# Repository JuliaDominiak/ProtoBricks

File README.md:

# ProtoBricks
## code_brickPlate_4x4<br />
The version is designed for a 4x4 tile<br />

 * **Brickplate_mini.ino** - the main program<br />
 * **MPR_connections.ino** - connecting with touch and color sensors<br />
 * **cap_1.ino** - displaying data from the first sensor<br />
 * **cap_2.ino** - displaying data from the second sensor<br />
 * **color.ino** - perform a color scan and decode RGB values<br />
 * **location.ino** - locate the pin for spike detection<br />
 * **decoding.ino** - decoding the location.ino number from the pin to the XY coordinates<br />

| Color  |No.|               
| ------ | - |               
| Red    | 1 |
| Blue   | 2 |
| Grey   | 3 |               
| Orange | 4 |               
| Yellow | 5 |
| Green  | 6 |

Touch sensor addresses - 0x5C, 0x5A<br />
Touch detection threshold: 150<br />

Pin functions<br />
pin 10 - adding / removing bricks<br />
pin 8 - color detection<br />

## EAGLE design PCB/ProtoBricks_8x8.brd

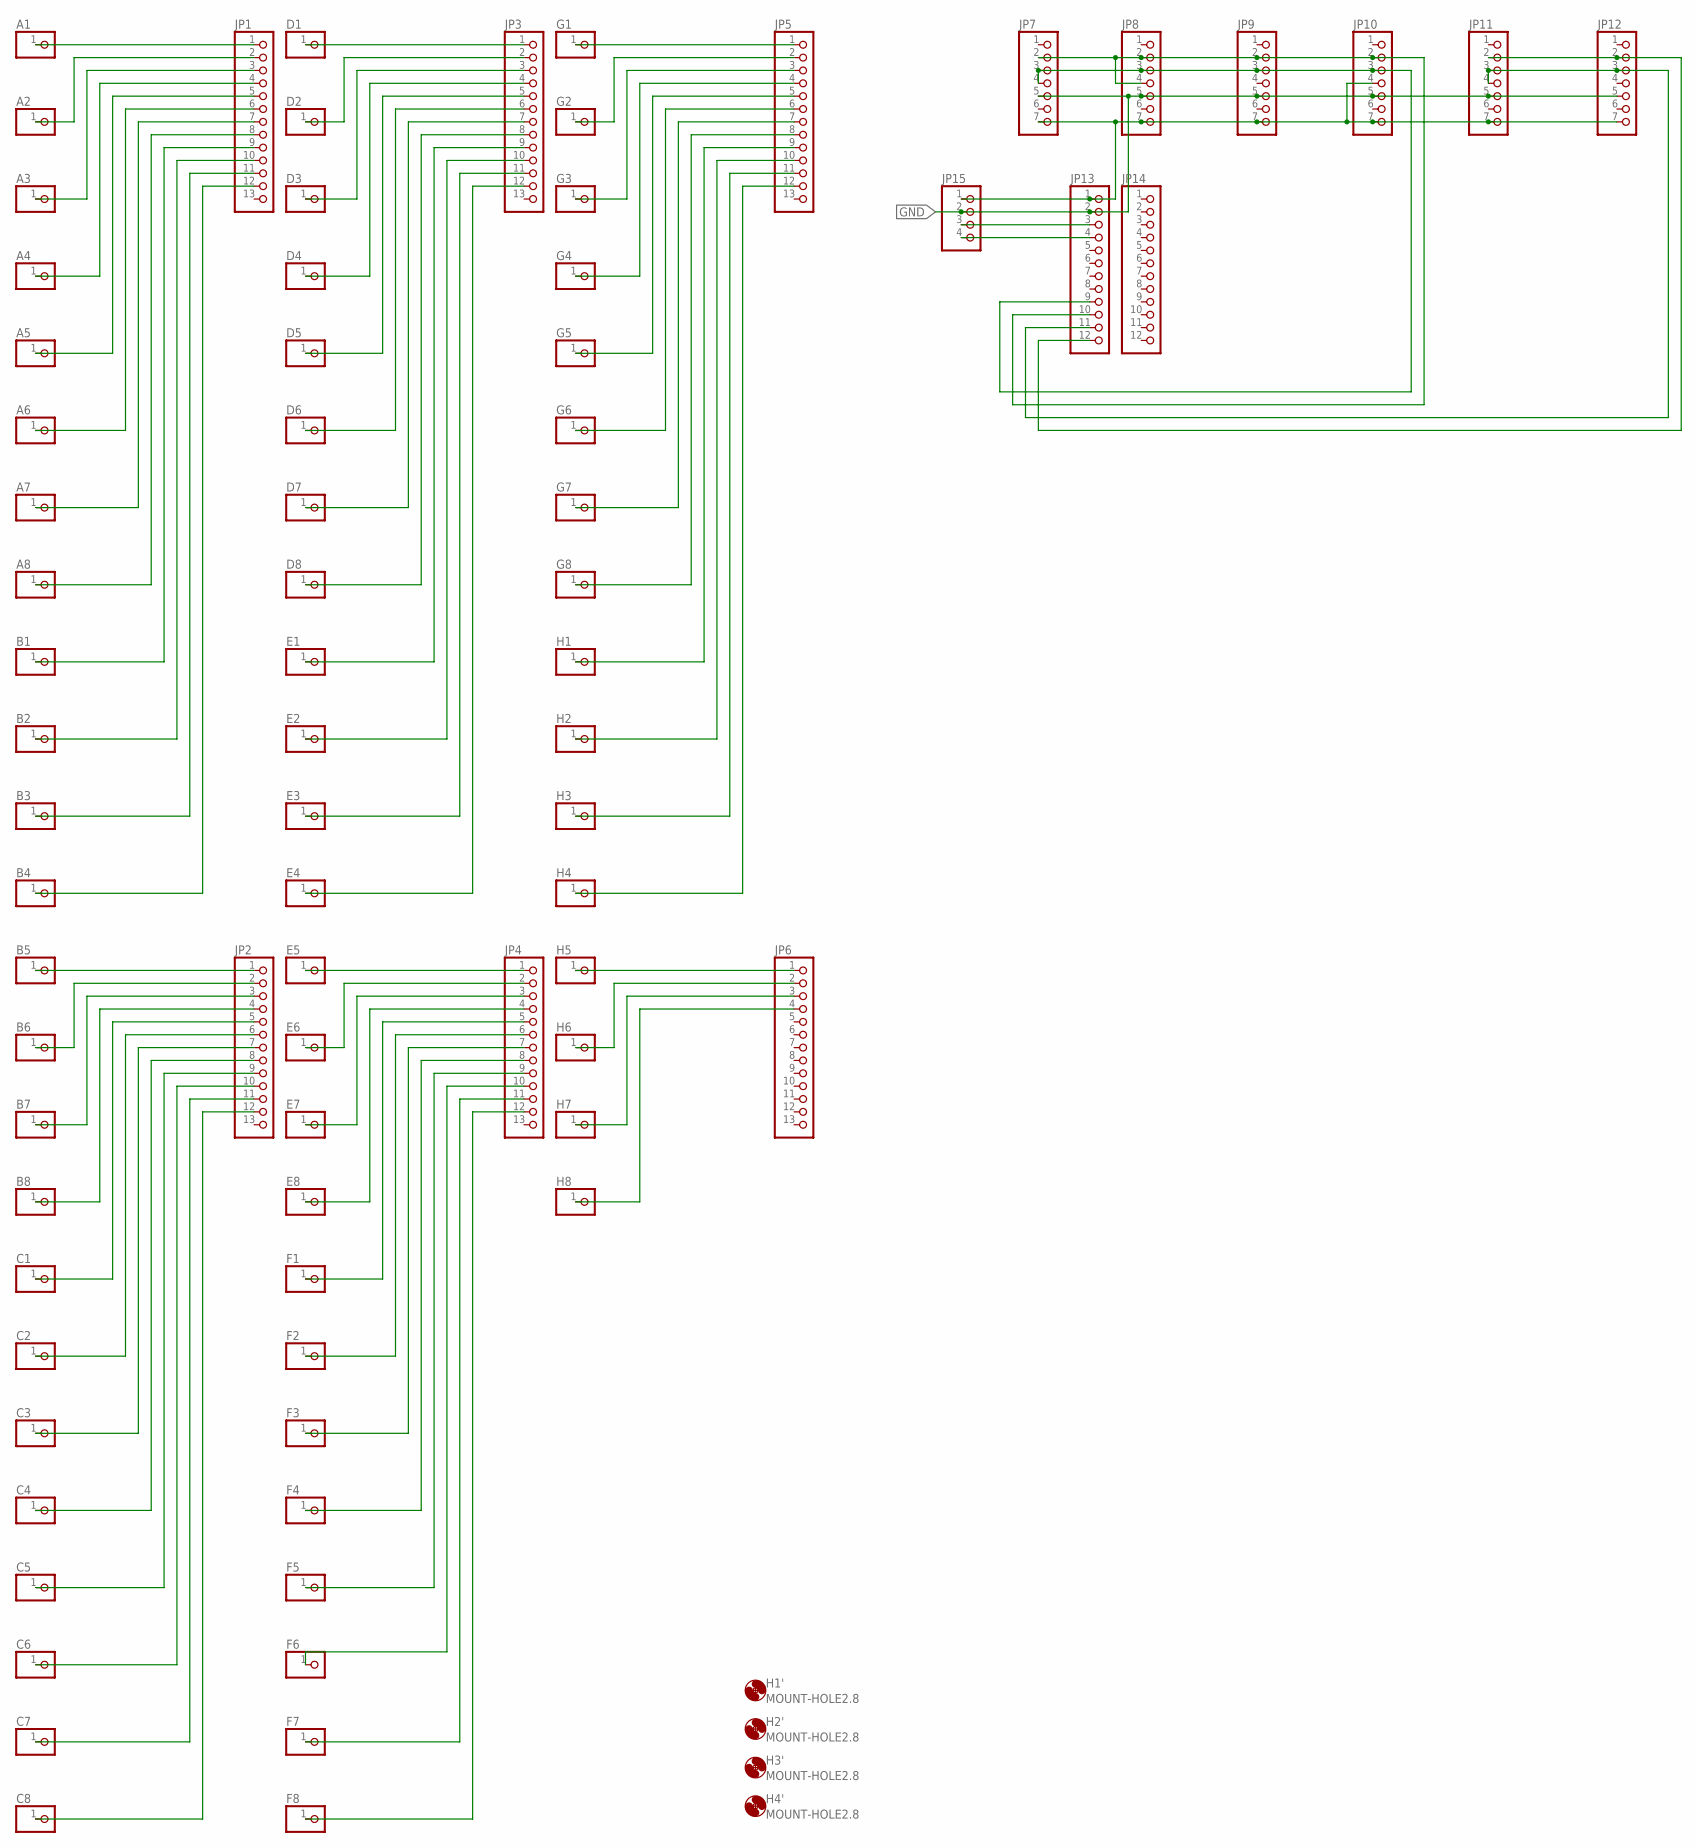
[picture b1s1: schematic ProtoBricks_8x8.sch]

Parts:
A1, A2, A3, A4, A5, A6, A7, A8: PINHD-1X1; 1X01
B1, B2, B3, B4, B5, B6, B7, B8: PINHD-1X1; 1X01
C1, C2, C3, C4, C5, C6, C7, C8: PINHD-1X1; 1X01
D1, D2, D3, D4, D5, D6, D7, D8: PINHD-1X1; 1X01
E1, E2, E3, E4, E5, E6, E7, E8: PINHD-1X1; 1X01
F1, F2, F3, F4, F5, F6, F7, F8: PINHD-1X1; 1X01
G1, G2, G3, G4, G5, G6, G7, G8: PINHD-1X1; 1X01
H1, H2, H3, H4, H5, H6, H7, H8: PINHD-1X1; 1X01
H1', H2', H3', H4': MOUNT-HOLE2.8; 2,8
JP1, JP2, JP3, JP4, JP5, JP6: PINHD-1X13; 1X13
JP7, JP8, JP9, JP10, JP11, JP12: PINHD-1X7; 1X07
JP13, JP14: PINHD-1X12; 1X12
JP15: PINHD-1X4; 1X04

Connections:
GND: JP7.5, JP8.5, JP9.5, JP10.5, JP11.5, JP12.5, JP13.2, JP15.2
unnamed: A1.1, JP1.1
unnamed: A2.1, JP1.2
unnamed: B5.1, JP2.1
unnamed: A3.1, JP1.3
unnamed: A4.1, JP1.4
unnamed: A5.1, JP1.5
unnamed: A6.1, JP1.6
unnamed: A7.1, JP1.7
unnamed: A8.1, JP1.8
unnamed: B1.1, JP1.9
unnamed: C8.1, JP2.12
unnamed: C7.1, JP2.11
unnamed: C6.1, JP2.10
unnamed: C5.1, JP2.9
unnamed: C4.1, JP2.8
unnamed: B2.1, JP1.10
unnamed: C3.1, JP2.7
unnamed: C2.1, JP2.6
unnamed: C1.1, JP2.5
unnamed: B8.1, JP2.4
unnamed: D1.1, JP3.1
unnamed: B7.1, JP2.3
unnamed: B6.1, JP2.2
unnamed: D2.1, JP3.2
unnamed: B3.1, JP1.11
unnamed: D3.1, JP3.3
unnamed: D4.1, JP3.4
unnamed: D5.1, JP3.5
unnamed: D6.1, JP3.6
unnamed: D7.1, JP3.7
unnamed: D8.1, JP3.8
unnamed: B4.1, JP1.12
unnamed: E1.1, JP3.9
unnamed: E2.1, JP3.10
unnamed: E3.1, JP3.11
unnamed: E4.1, JP3.12
unnamed: E5.1, JP4.1
unnamed: E6.1, JP4.2
unnamed: E7.1, JP4.3
unnamed: E8.1, JP4.4
unnamed: G1.1, JP5.1
unnamed: G2.1, JP5.2
unnamed: G3.1, JP5.3
unnamed: G4.1, JP5.4
unnamed: G5.1, JP5.5
unnamed: G6.1, JP5.6
unnamed: G7.1, JP5.7
unnamed: G8.1, JP5.8
unnamed: H1.1, JP5.9
unnamed: H2.1, JP5.10
unnamed: H3.1, JP5.11
unnamed: H4.1, JP5.12
unnamed: H5.1, JP6.1
unnamed: H6.1, JP6.2
unnamed: H7.1, JP6.3
unnamed: H8.1, JP6.4
unnamed: F1.1, JP4.5
unnamed: F2.1, JP4.6
unnamed: F3.1, JP4.7
unnamed: F4.1, JP4.8
unnamed: F5.1, JP4.9
unnamed: F6.1, JP4.10
unnamed: F7.1, JP4.11
unnamed: F8.1, JP4.12
unnamed: JP7.2, JP8.2, JP8.4, JP9.2, JP10.2, JP13.10
unnamed: JP7.3, JP7.4, JP8.3, JP9.3, JP10.3, JP13.9
unnamed: JP11.2, JP12.2, JP13.12
unnamed: JP11.3, JP11.4, JP12.3, JP13.11
unnamed: JP7.7, JP8.7, JP9.7, JP10.4, JP10.7, JP11.7, JP12.7, JP13.1, JP15.1
unnamed: JP13.3, JP15.3
unnamed: JP13.4, JP15.4

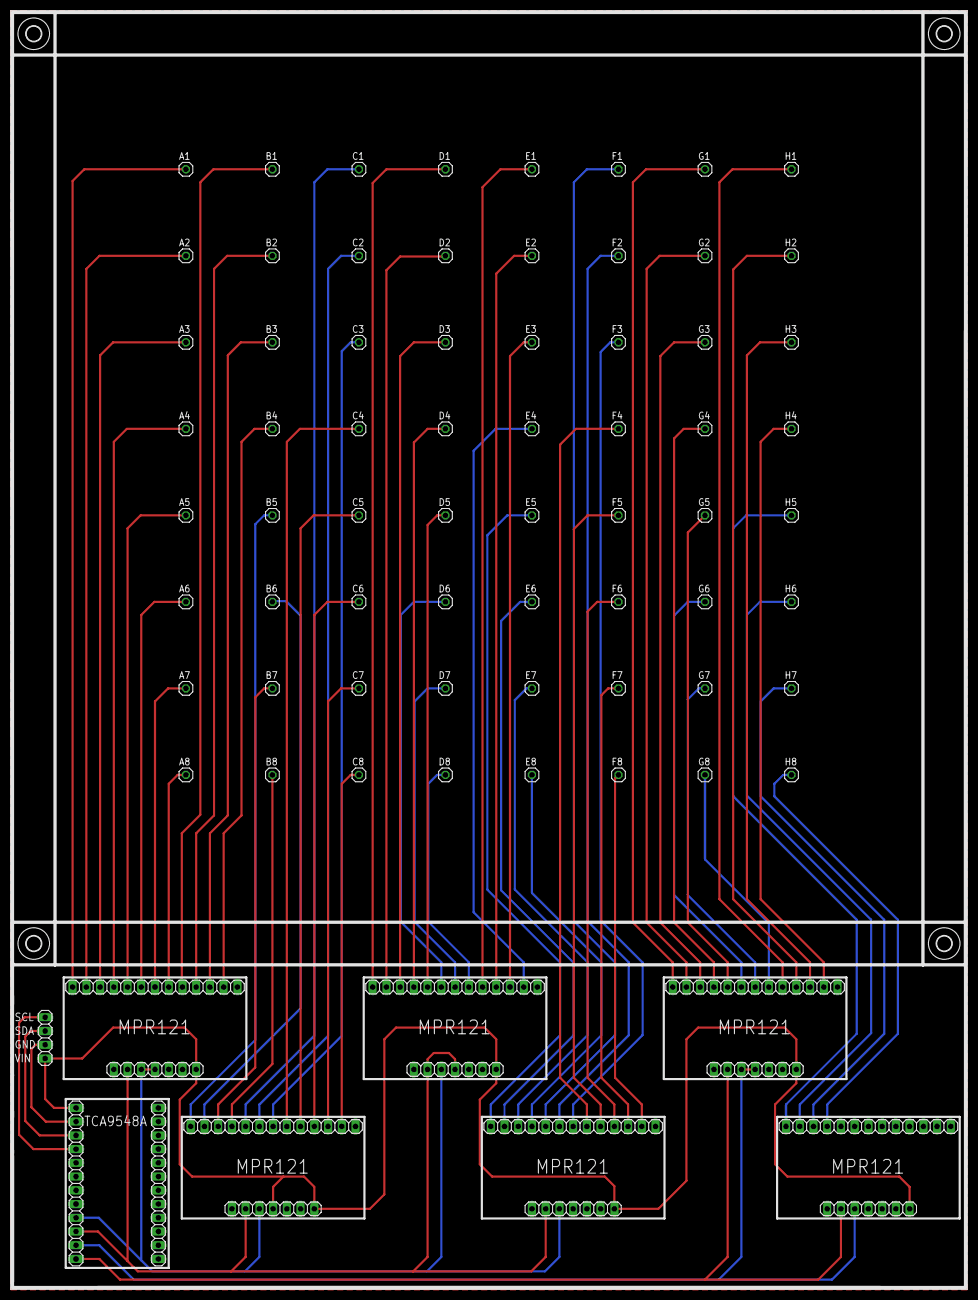
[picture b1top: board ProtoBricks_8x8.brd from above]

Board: 2 copper layers, 176.9 x 236.4 mm, 83 parts (0 on the bottom side), 72 nets.

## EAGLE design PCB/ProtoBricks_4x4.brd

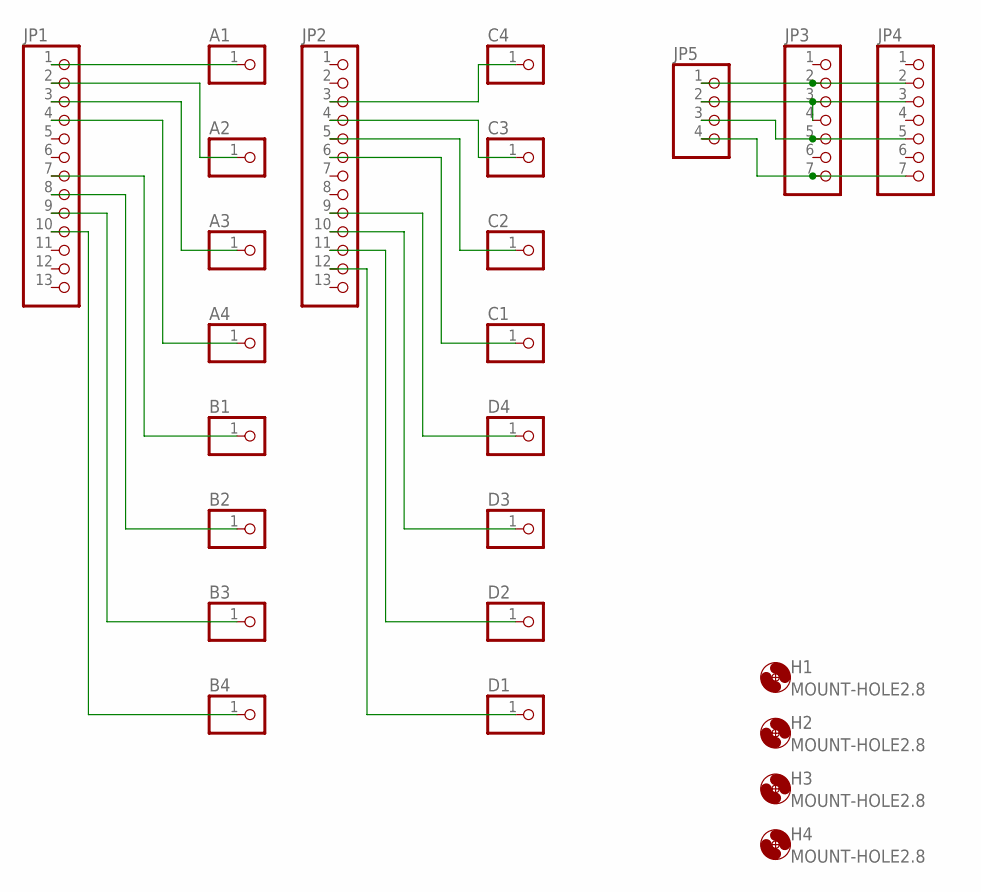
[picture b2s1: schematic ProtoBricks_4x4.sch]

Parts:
A1, A2, A3, A4: PINHD-1X1; 1X01
B1, B2, B3, B4: PINHD-1X1; 1X01
C1, C2, C3, C4: PINHD-1X1; 1X01
D1, D2, D3, D4: PINHD-1X1; 1X01
H1, H2, H3, H4: MOUNT-HOLE2.8; 2,8
JP1, JP2: PINHD-1X13; 1X13
JP3, JP4: PINHD-1X7; 1X07
JP5: PINHD-1X4; 1X04

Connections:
GND: JP3.5, JP4.5, JP5.3
unnamed: A1.1, JP1.1
unnamed: A2.1, JP1.2
unnamed: A3.1, JP1.3
unnamed: A4.1, JP1.4
unnamed: C1.1, JP2.6
unnamed: B4.1, JP1.10
unnamed: B3.1, JP1.9
unnamed: C2.1, JP2.5
unnamed: C3.1, JP2.4
unnamed: C4.1, JP2.3
unnamed: JP3.2, JP4.2, JP5.1
unnamed: JP3.3, JP3.4, JP4.3, JP5.2
unnamed: D4.1, JP2.9
unnamed: D3.1, JP2.10
unnamed: D2.1, JP2.11
unnamed: D1.1, JP2.12
unnamed: JP3.7, JP4.7, JP5.4
unnamed: B1.1, JP1.7
unnamed: B2.1, JP1.8

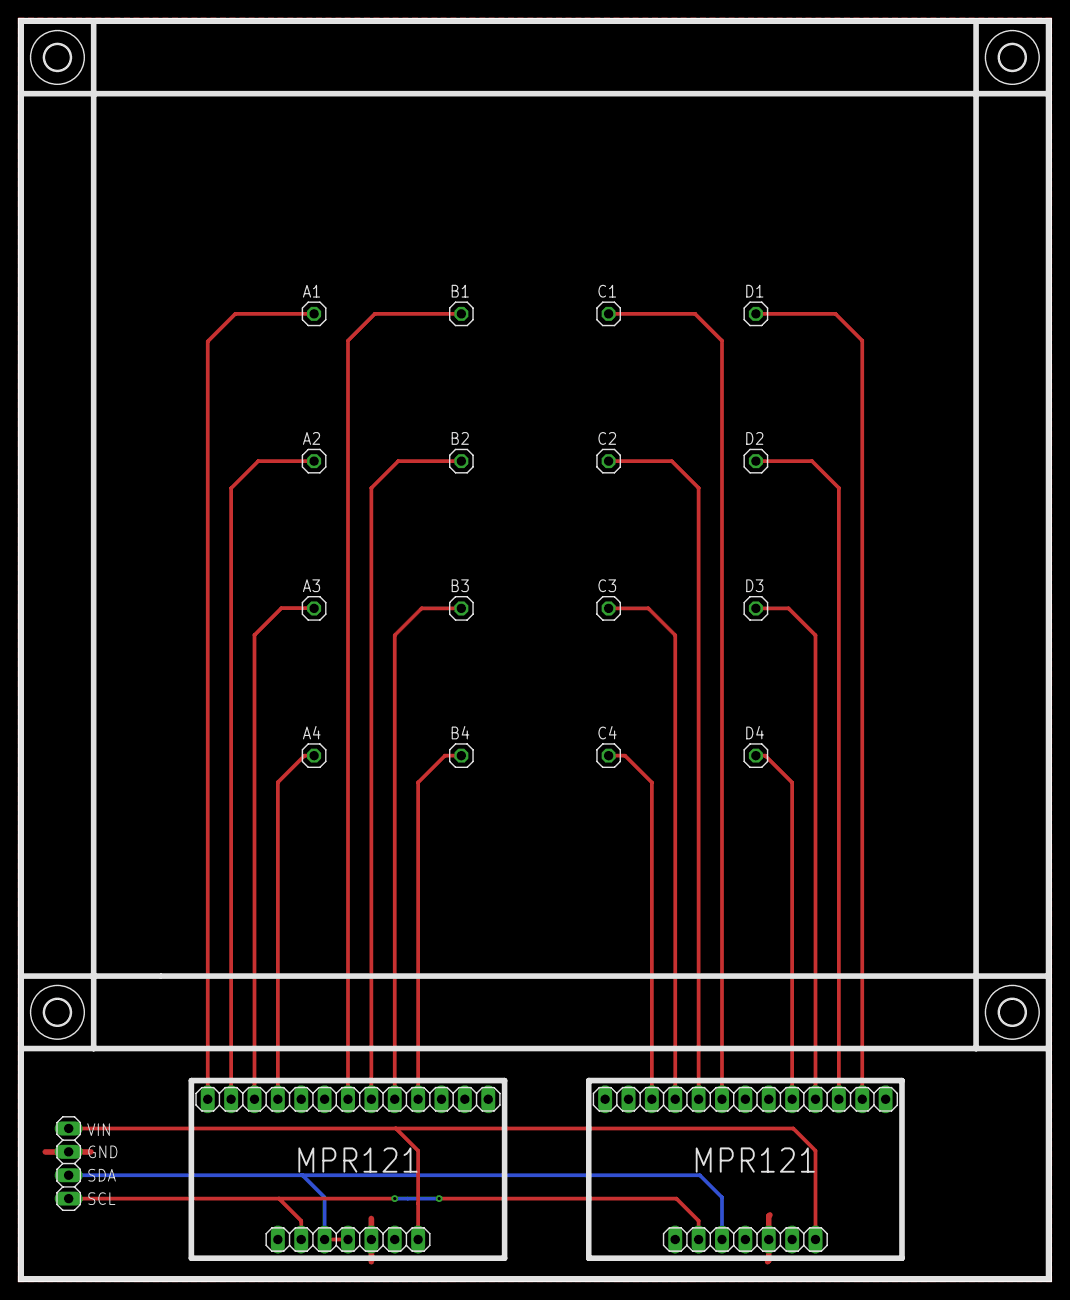
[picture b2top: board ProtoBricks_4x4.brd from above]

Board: 2 copper layers, 112.2 x 137.3 mm, 25 parts (0 on the bottom side), 20 nets.

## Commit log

2023-06-07 Create LEGO_3D_models
2024-05-05 Update and rename
